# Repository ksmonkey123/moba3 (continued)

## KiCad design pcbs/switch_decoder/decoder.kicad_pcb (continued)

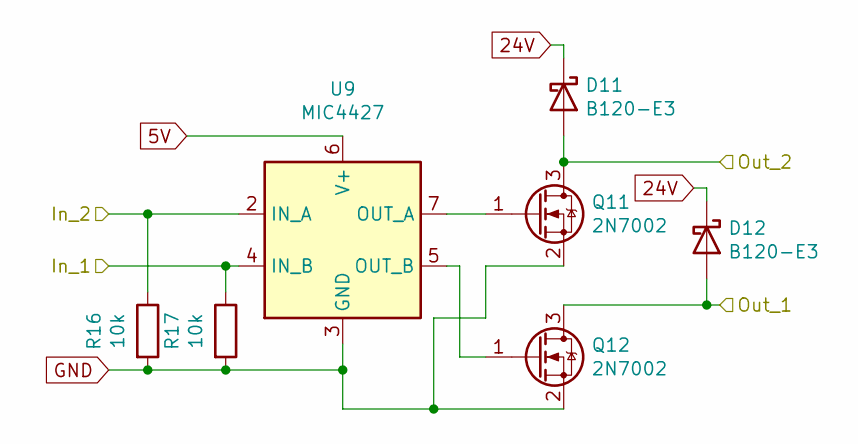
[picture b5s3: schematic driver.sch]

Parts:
D1, D2: B120-E3; D_SMA
Q1, Q2: 2N7002; SOT-23
R6, R7: 10k; R_0603_1608Metric
U3: MIC4427; SOIC-8_3.9x4.9mm_P1.27mm

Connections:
5V: U3.6 (V+); also elsewhere on the board
24V: D1.1 (K), D2.1 (K); also elsewhere on the board
/switch 1/Out_1: D2.2 (A), Q2.3 (D); also elsewhere on the board
/switch 1/Out_2: D1.2 (A), Q1.3 (D); also elsewhere on the board
GND: Q1.2 (S), Q2.2 (S), R6.2, U3.3 (GND); also elsewhere on the board
unnamed: Q1.1 (G), U3.7 (OUT_A)
unnamed: Q2.1 (G), U3.5 (OUT_B)

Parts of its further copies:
D3, D4, D5, D6, D7, D8, D9, D10, D11, D12: B120-E3; D_SMA
Q3, Q4, Q5, Q6, Q7, Q8, Q9, Q10, Q11, Q12: 2N7002; SOT-23
R4, R5, R9, R10, R11, R12, R13, R14, R15, R16, R17: 10k; R_0603_1608Metric
U5, U6, U7, U8, U9: MIC4427; SOIC-8_3.9x4.9mm_P1.27mm

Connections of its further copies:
5V: U5.6 (V+), U6.6 (V+), U7.6 (V+), U8.6 (V+), U9.6 (V+); also elsewhere on the board
24V: D3.1 (K), D4.1 (K), D5.1 (K), D6.1 (K), D7.1 (K), D8.1 (K), D9.1 (K), D10.1 (K), D11.1 (K), D12.1 (K); also elsewhere on the board
/switch 2/In_1: R9.1, U5.4 (IN_B); also elsewhere on the board
/switch 2/Out_1: D4.2 (A), Q4.3 (D); also elsewhere on the board
/switch 2/Out_2: D3.2 (A), Q3.3 (D); also elsewhere on the board
/switch 3/In_1: R11.1, U6.4 (IN_B); also elsewhere on the board
/switch 3/In_2: R10.1, U6.2 (IN_A); also elsewhere on the board
/switch 3/Out_1: D6.2 (A), Q6.3 (D); also elsewhere on the board
/switch 3/Out_2: D5.2 (A), Q5.3 (D); also elsewhere on the board
/switch 4/In_1: R13.1, U7.4 (IN_B); also elsewhere on the board
/switch 4/Out_1: D8.2 (A), Q8.3 (D); also elsewhere on the board
/switch 4/Out_2: D7.2 (A), Q7.3 (D); also elsewhere on the board
/switch 5/In_1: R15.1, U8.4 (IN_B); also elsewhere on the board
/switch 5/In_2: R14.1, U8.2 (IN_A); also elsewhere on the board
/switch 5/Out_1: D10.2 (A), Q10.3 (D); also elsewhere on the board
/switch 5/Out_2: D9.2 (A), Q9.3 (D); also elsewhere on the board
/switch 6/In_1: R17.1, U9.4 (IN_B); also elsewhere on the board
/switch 6/In_2: R16.1, U9.2 (IN_A); also elsewhere on the board
/switch 6/Out_1: D12.2 (A), Q12.3 (D); also elsewhere on the board
/switch 6/Out_2: D11.2 (A), Q11.3 (D); also elsewhere on the board
GND: Q3.2 (S), Q4.2 (S), Q5.2 (S), Q6.2 (S), Q7.2 (S), Q8.2 (S), Q9.2 (S), Q10.2 (S), Q11.2 (S), Q12.2 (S), R4.2, R5.2, R9.2, R10.2, R11.2, R12.2, R13.2, R14.2, R15.2, R16.2, R17.2, U5.3 (GND), U6.3 (GND), U7.3 (GND), U8.3 (GND), U9.3 (GND); also elsewhere on the board
unnamed: Q3.1 (G), U5.7 (OUT_A)
unnamed: Q4.1 (G), U5.5 (OUT_B)
unnamed: Q5.1 (G), U6.7 (OUT_A)
unnamed: Q6.1 (G), U6.5 (OUT_B)
unnamed: Q7.1 (G), U7.7 (OUT_A)
unnamed: Q8.1 (G), U7.5 (OUT_B)
unnamed: Q9.1 (G), U8.7 (OUT_A)
unnamed: Q10.1 (G), U8.5 (OUT_B)
unnamed: Q11.1 (G), U9.7 (OUT_A)
unnamed: Q12.1 (G), U9.5 (OUT_B)

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
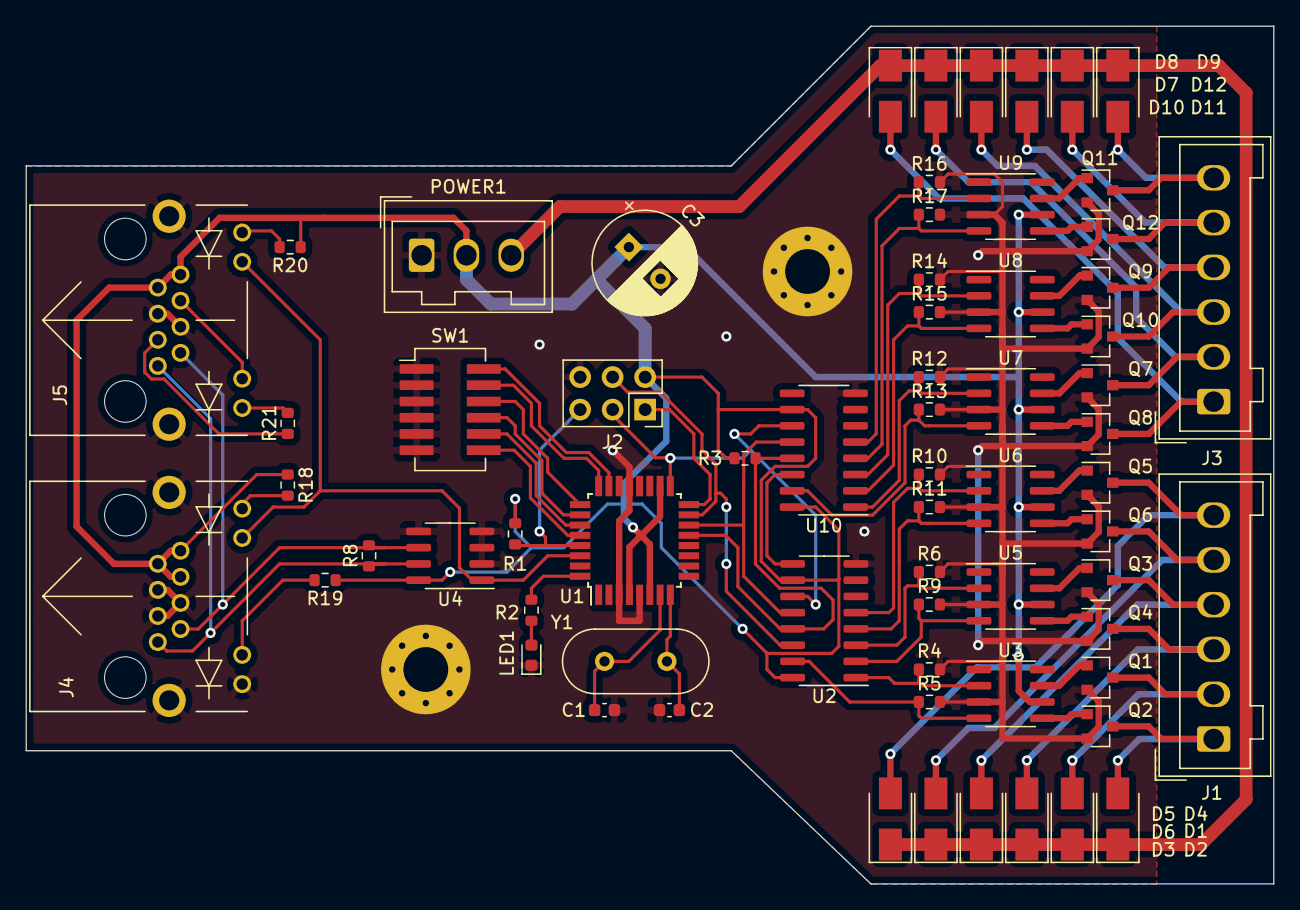
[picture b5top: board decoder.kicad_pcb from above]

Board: 2 copper layers, 97.5 x 67.1 mm, 68 parts (1 on the bottom side), 65 nets.

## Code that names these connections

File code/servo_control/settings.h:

#include <Arduino.h>

#define PIN_SERVO A3

#define PIN_LED_A 0
#define PIN_LED_B A1
#define PIN_LED_C 10

#define PIN_TOGGLE A4
#define PIN_TRIGGER_A 8
#define PIN_TRIGGER_B 9

#define PIN_CALIBRATION_A A5
#define PIN_CALIBRATION_B A2

#define BOOT_DELAY_MS 500

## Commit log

2021-05-30 decoder boards and code
2021-05-30 started controller code
2021-06-01 first switch controller
2021-06-01 directory for controller modules specifically
2021-06-02 I/O LEDS & yard implementation (legacy)
2021-06-02 reference images
2021-06-05 started bugfixing
2021-06-19 produced PCBs, dropped baudrate, removed on-board dynamic address selection - decoder must now be configured via programmer!
2021-06-19 cleanup
2021-07-13 revision b of boards
2021-07-13 decoder tweaks: status led, no more masking, no external config, slower baudrate
2021-08-09 dark mode
2021-09-06 finished railway control elements
2021-09-07 basic implementation of I/O board
    closes #1
2021-09-07 staggered switch commands
    switch commands are now transmitted over time instead of all at once. this reduces load on power delivery circuitry. closes #2
2021-09-07 redriving command for switch decoders
    allow the controller to order switch decoders to re-drive a switch to a previously transmitted state. This can be used to force the switch back into the correct position after e.g. moving it by hand.
    closes #3
2021-09-07 force switch re-driving when switch PSU is enabled
    whenever the switch PSU is enabled, force all switch drivers to drive their switches again. closes #4
    also some cleanup of debug logging. previously logging messages took up 30% of used static memory... now only timer creation is logged and log messages use only 18 bytes of memory.
2021-09-07 cleanup
    removed another unnecessary log message. Logging now only uses 2 bytes of static memory
2021-09-08 forced update after switch PSU enabling is delayed by 1 switch staggering period to allow the PSU time to stabilize
2021-09-08 retransmission support
    closes #5
2021-09-29 revised exit signal decoder
2021-10-01 pcb reference pictures
2021-10-01 cropped pcb reference pictures
2021-10-01 reworked exit signal controllers
2021-10-01 started documentation
2021-10-03 documentation
2021-10-03 button command specification
2021-10-04 finished hardware documentation
2021-10-04 formatting
2021-10-05 review pass
2021-10-09 completed rev A of documentation
2021-10-09 fixed #11 - light decoders now use big-endian hex encoding
2021-11-01 migration to async, basic light control
    closes #6
    cleanup
2021-11-04 documentation & normalisation of distance signal if home signal is showing HALT
2021-11-05 staggered light updates
    added pulsed button feature for simpler testing
2021-11-05 bugfixing and rework
2021-11-05 docs revision
2021-11-05 rev B fixes
2021-11-25 bugfixes
2021-11-25 fixed IOIB not communicating properly with CTRB
    windows linebreaks in Serial.println()....
2021-11-25 documentation update
2021-11-27 made controller tolerant of \r
2021-11-28 testing fixes:
    CTRB:
    - fixed bad routing in right station entry
    - fixed left station signals not clearing with paths
    - disabled forced switch updates
    IOIB:
    - status led blinking when display data changes
2021-12-09 servo driver
2021-12-11 servo driver rev. A
2021-12-12 improved servo control (disable position sensing during switching cycle to reduce overshoot)
2021-12-20 Rev. A servo board
2021-12-20 servo revisions
2022-11-25 controller shield rev. A and code support
2022-11-26 proxy mode for controller
    proxy mode allows a user connected to the controller via USB to open a direct proxy channel to the remote bus: the controller reads incoming data (from USB) and forwards it to the busses. IOIB data i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
2022-12-14 multi-sample button handling in I/O board
    single-sample processing is vulnerable to sampling errors (interference effects, stray capacitances, etc...).
    as a solution we record 3 samples.
    only after 3 samples have been recorded, we process the data.
    Between the 3 samples majority rule is used for each bit. This allows masking of a single outlier within each sample.
    untested as of yet
2022-12-25 IOIB: min delay between samples
2022-12-25 CTRB: fixed signal aspects sometimes not updated when clearing a station path
2022-12-25 CTRB: faster startup, faster path upgrades
2022-12-25 CTRB: debug log of key presses
2024-03-02 add debouncing for io buttons
